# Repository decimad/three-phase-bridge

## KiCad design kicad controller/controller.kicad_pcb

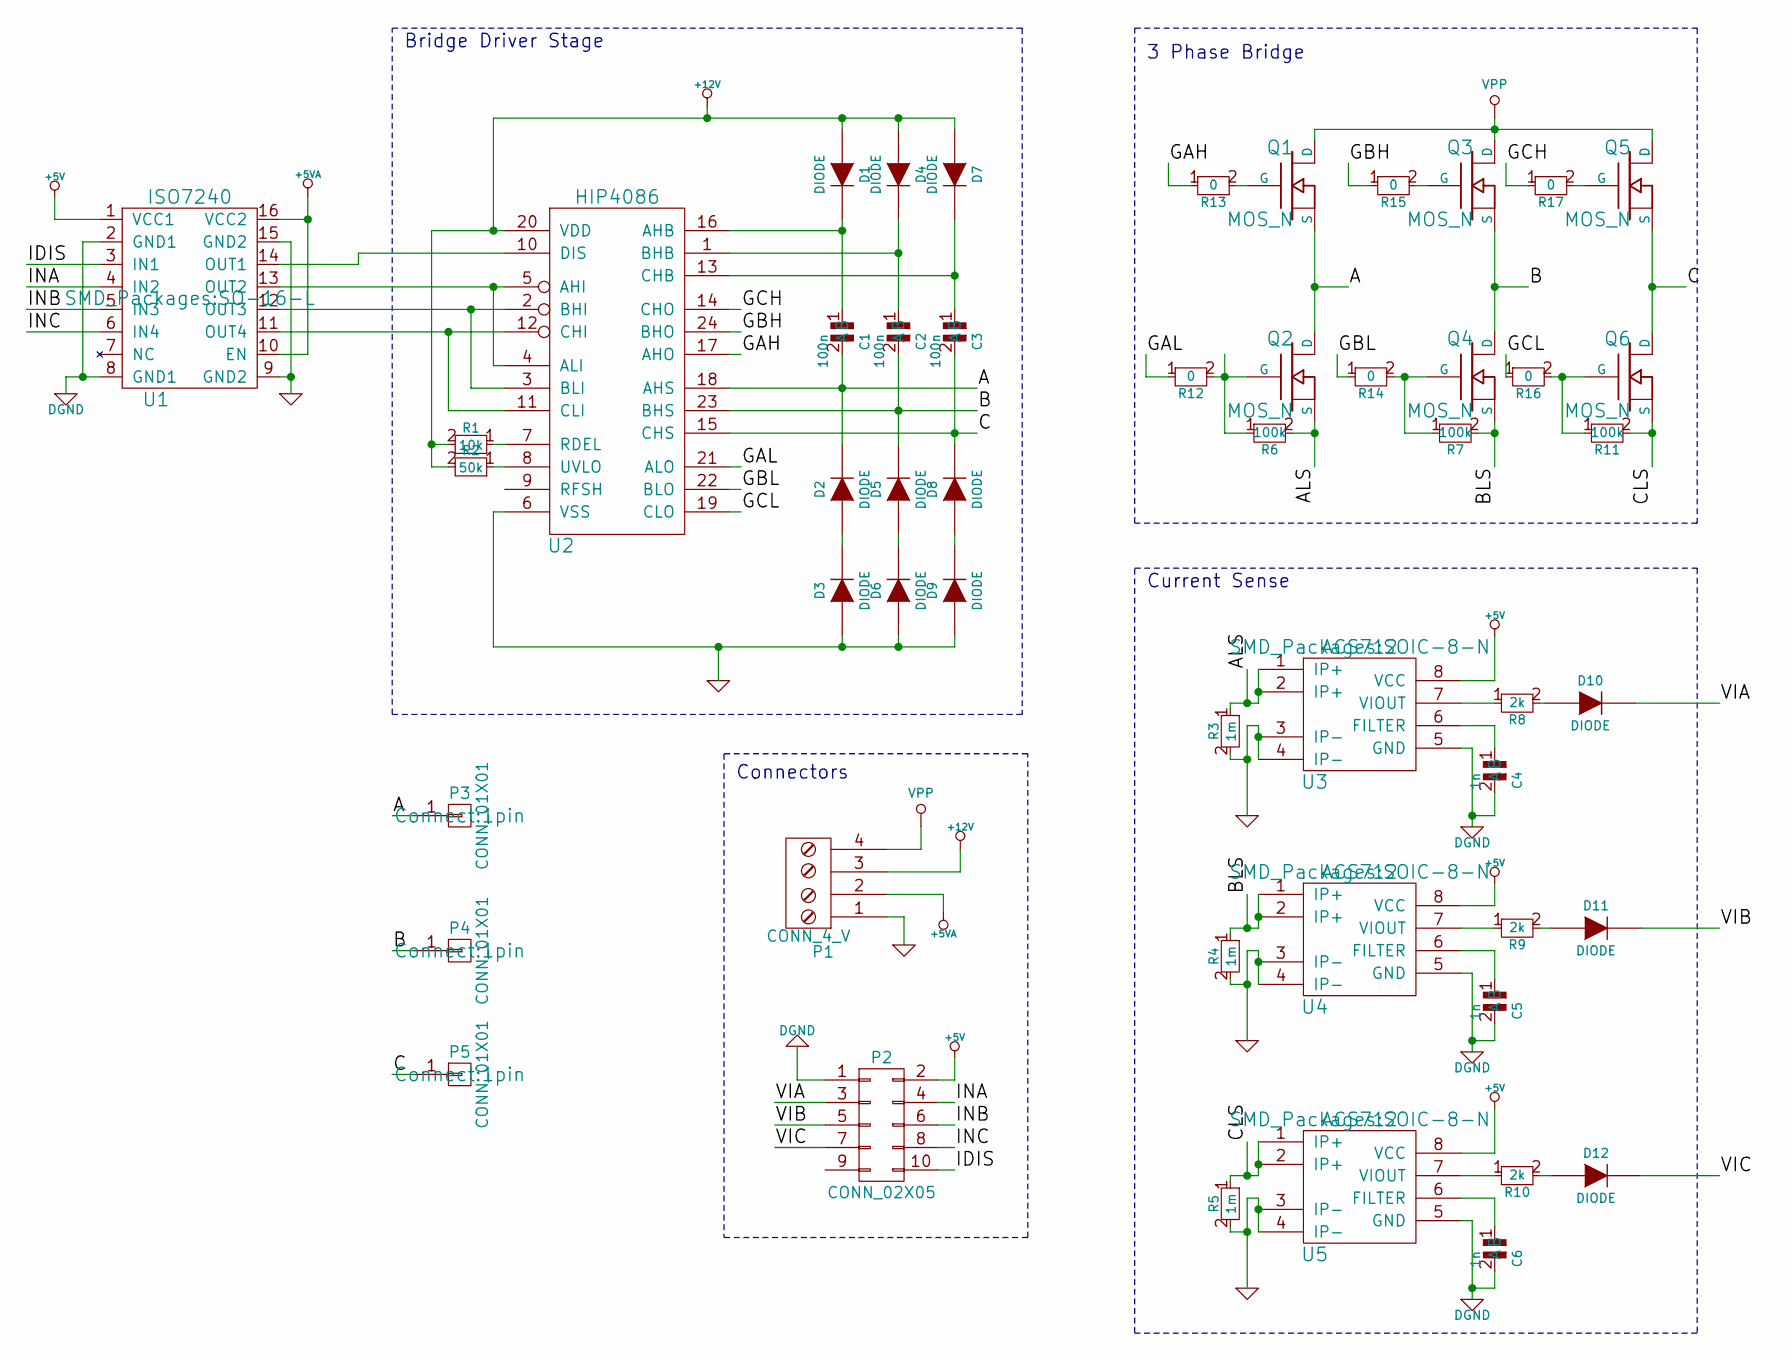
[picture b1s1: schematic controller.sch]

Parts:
C1, C2, C3: 100n; SMD-0603_r
C4, C5, C6: 1n; SMD-0603_r
D1, D2, D3, D4, D5, D6, D7, D8, D9, D10, D11, D12: DIODE; SMD-0603_r
P1: CONN_4_V; bornier4
P2: CONN_02X05; Pin_Header_Straight_2x05
P3, P4, P5: CONN_01X01; 1pin
PWR_MAIN1, PWR_MAIN2: VPP
Q1, Q2, Q3, Q4, Q5, Q6: MOS_N; SOT669_5b98489ea2fa4cc583322cef259052cd
R1: 10k; SMD-0603_r
R2: 50k; SMD-0603_r
R3, R4, R5: 1m; SMD-0603_r
R6, R7, R11: 100k; SMD-0603_r
R8, R9, R10: 2k; SMD-0603_r
R12, R13, R14, R15, R16, R17: 0; SMD-1206
U1: ISO7240; SO-16-L
U2: HIP4086; SOIC-24_7.5x15.4mm_Pitch1.27mm
U3, U4, U5: ACS712; SOIC-8-N

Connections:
+5V: P2.2, U1.1 (VCC1), U3.8 (VCC), U4.8 (VCC), U5.8 (VCC)
+5VA: P1.2, U1.10 (EN), U1.16 (VCC2)
+12V: D1.1 (A), D4.1 (A), D7.1 (A), P1.3, R1.2, R2.2, U2.20 (VDD)
/A: C1.2 (B), D2.2 (K), P3.1, Q1.S, Q2.D, U2.18 (AHS)
/ALS: Q2.S, R3.1, R6.2, U3.1 (IP+), U3.2 (IP+)
/B: C2.2 (B), D5.2 (K), P4.1, Q3.S, Q4.D, U2.23 (BHS)
/BLS: Q4.S, R4.1, R7.2, U4.1 (IP+), U4.2 (IP+)
/C: C3.2 (B), D8.2 (K), P5.1, Q5.S, Q6.D, U2.15 (CHS)
/CLS: Q6.S, R5.1, R11.2, U5.1 (IP+), U5.2 (IP+)
/GAH: R13.1, U2.17 (AHO)
/GAL: R12.1, U2.21 (ALO)
/GBH: R15.1, U2.24 (BHO)
/GBL: R14.1, U2.22 (BLO)
/GCH: R17.1, U2.14 (CHO)
/GCL: R16.1, U2.19 (CLO)
/IDIS: P2.10, U1.3 (IN1)
/INA: P2.4, U1.4 (IN2)
/INB: P2.6, U1.5 (IN3)
/INC: P2.8, U1.6 (IN4)
/VIA: D10.2 (K), P2.3
/VIB: D11.2 (K), P2.5
/VIC: D12.2 (K), P2.7
DGND: C4.2 (B), C5.2 (B), C6.2 (B), P2.1, U1.2 (GND1), U1.8 (GND1), U3.5 (GND), U4.5 (GND), U5.5 (GND)
GND: D3.1 (A), D6.1 (A), D9.1 (A), P1.1, R3.2, R4.2, R5.2, U1.9 (GND2), U1.15 (GND2), U2.6 (VSS), U3.3 (IP-), U3.4 (IP-), U4.3 (IP-), U4.4 (IP-), U5.3 (IP-), U5.4 (IP-)
unnamed: C1.1 (A), D1.2 (K), U2.16 (AHB)
unnamed: C2.1 (A), D4.2 (K), U2.1 (BHB)
unnamed: C3.1 (A), D7.2 (K), U2.13 (CHB)
unnamed: C4.1 (A), U3.6 (FILTER)
unnamed: C5.1 (A), U4.6 (FILTER)
unnamed: C6.1 (A), U5.6 (FILTER)
unnamed: D2.1 (A), D3.2 (K)
unnamed: D5.1 (A), D6.2 (K)
unnamed: D8.1 (A), D9.2 (K)
unnamed: D10.1 (A), R8.2
unnamed: D11.1 (A), R9.2
unnamed: D12.1 (A), R10.2
unnamed: Q1.G, R13.2
unnamed: Q2.G, R6.1, R12.2
unnamed: Q3.G, R15.2
unnamed: Q4.G, R7.1, R14.2
unnamed: Q5.G, R17.2
unnamed: Q6.G, R11.1, R16.2
unnamed: R1.1, U2.7 (RDEL)
unnamed: R2.1, U2.8 (UVLO)
unnamed: R8.1, U3.7 (VIOUT)
unnamed: R9.1, U4.7 (VIOUT)
unnamed: R10.1, U5.7 (VIOUT)
unnamed: U1.11 (OUT4), U2.11 (CLI), U2.12 (CHI)
unnamed: U1.12 (OUT3), U2.2 (BHI), U2.3 (BLI)
unnamed: U1.13 (OUT2), U2.4 (ALI), U2.5 (AHI)
unnamed: U1.14 (OUT1), U2.10 (DIS)

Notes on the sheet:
Current Sense
3 Phase Bridge
Bridge Driver Stage
Connectors

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
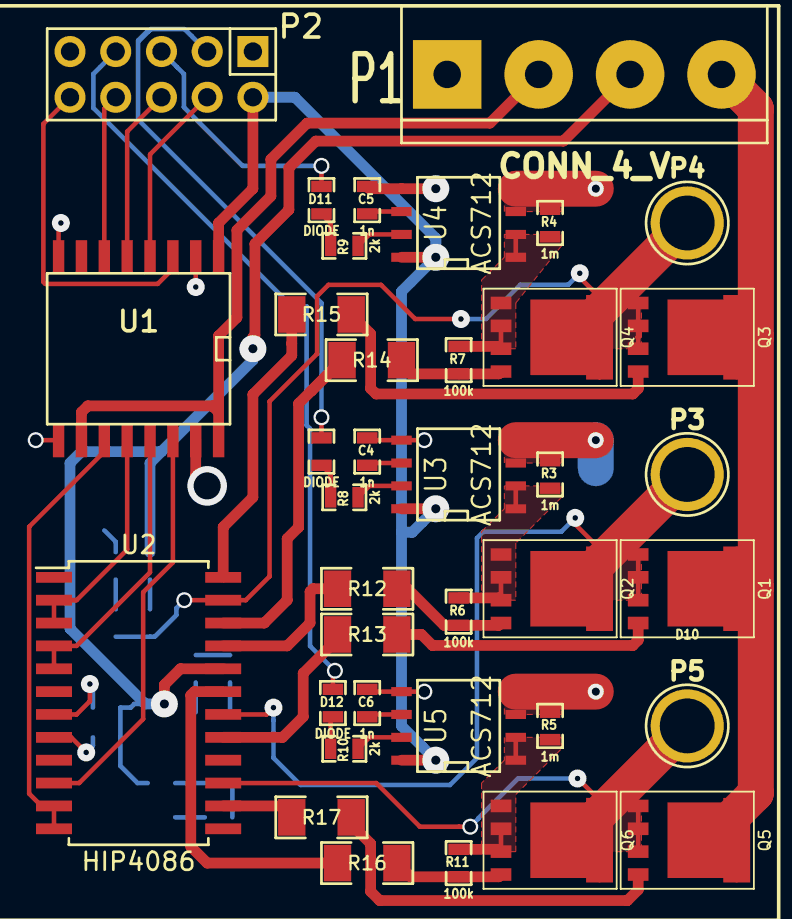
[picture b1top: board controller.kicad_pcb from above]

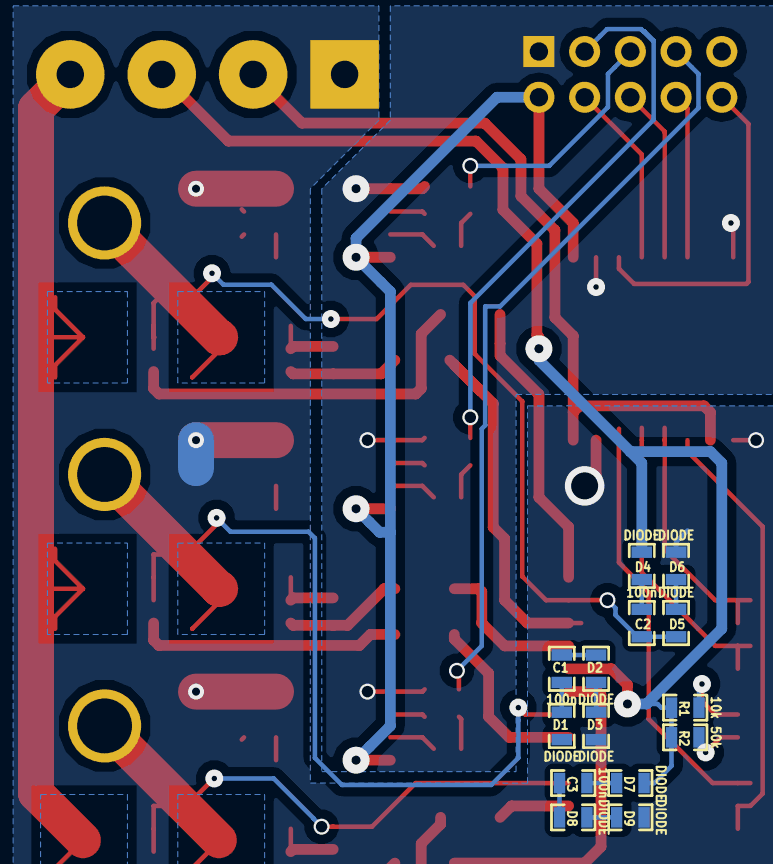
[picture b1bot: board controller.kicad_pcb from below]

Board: 2 copper layers, 51 parts (14 on the bottom side), 52 nets.

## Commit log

2014-12-07 updated pcd
2014-12-08 grml
2014-12-08 added thermals to mosfets
2014-12-08 images
